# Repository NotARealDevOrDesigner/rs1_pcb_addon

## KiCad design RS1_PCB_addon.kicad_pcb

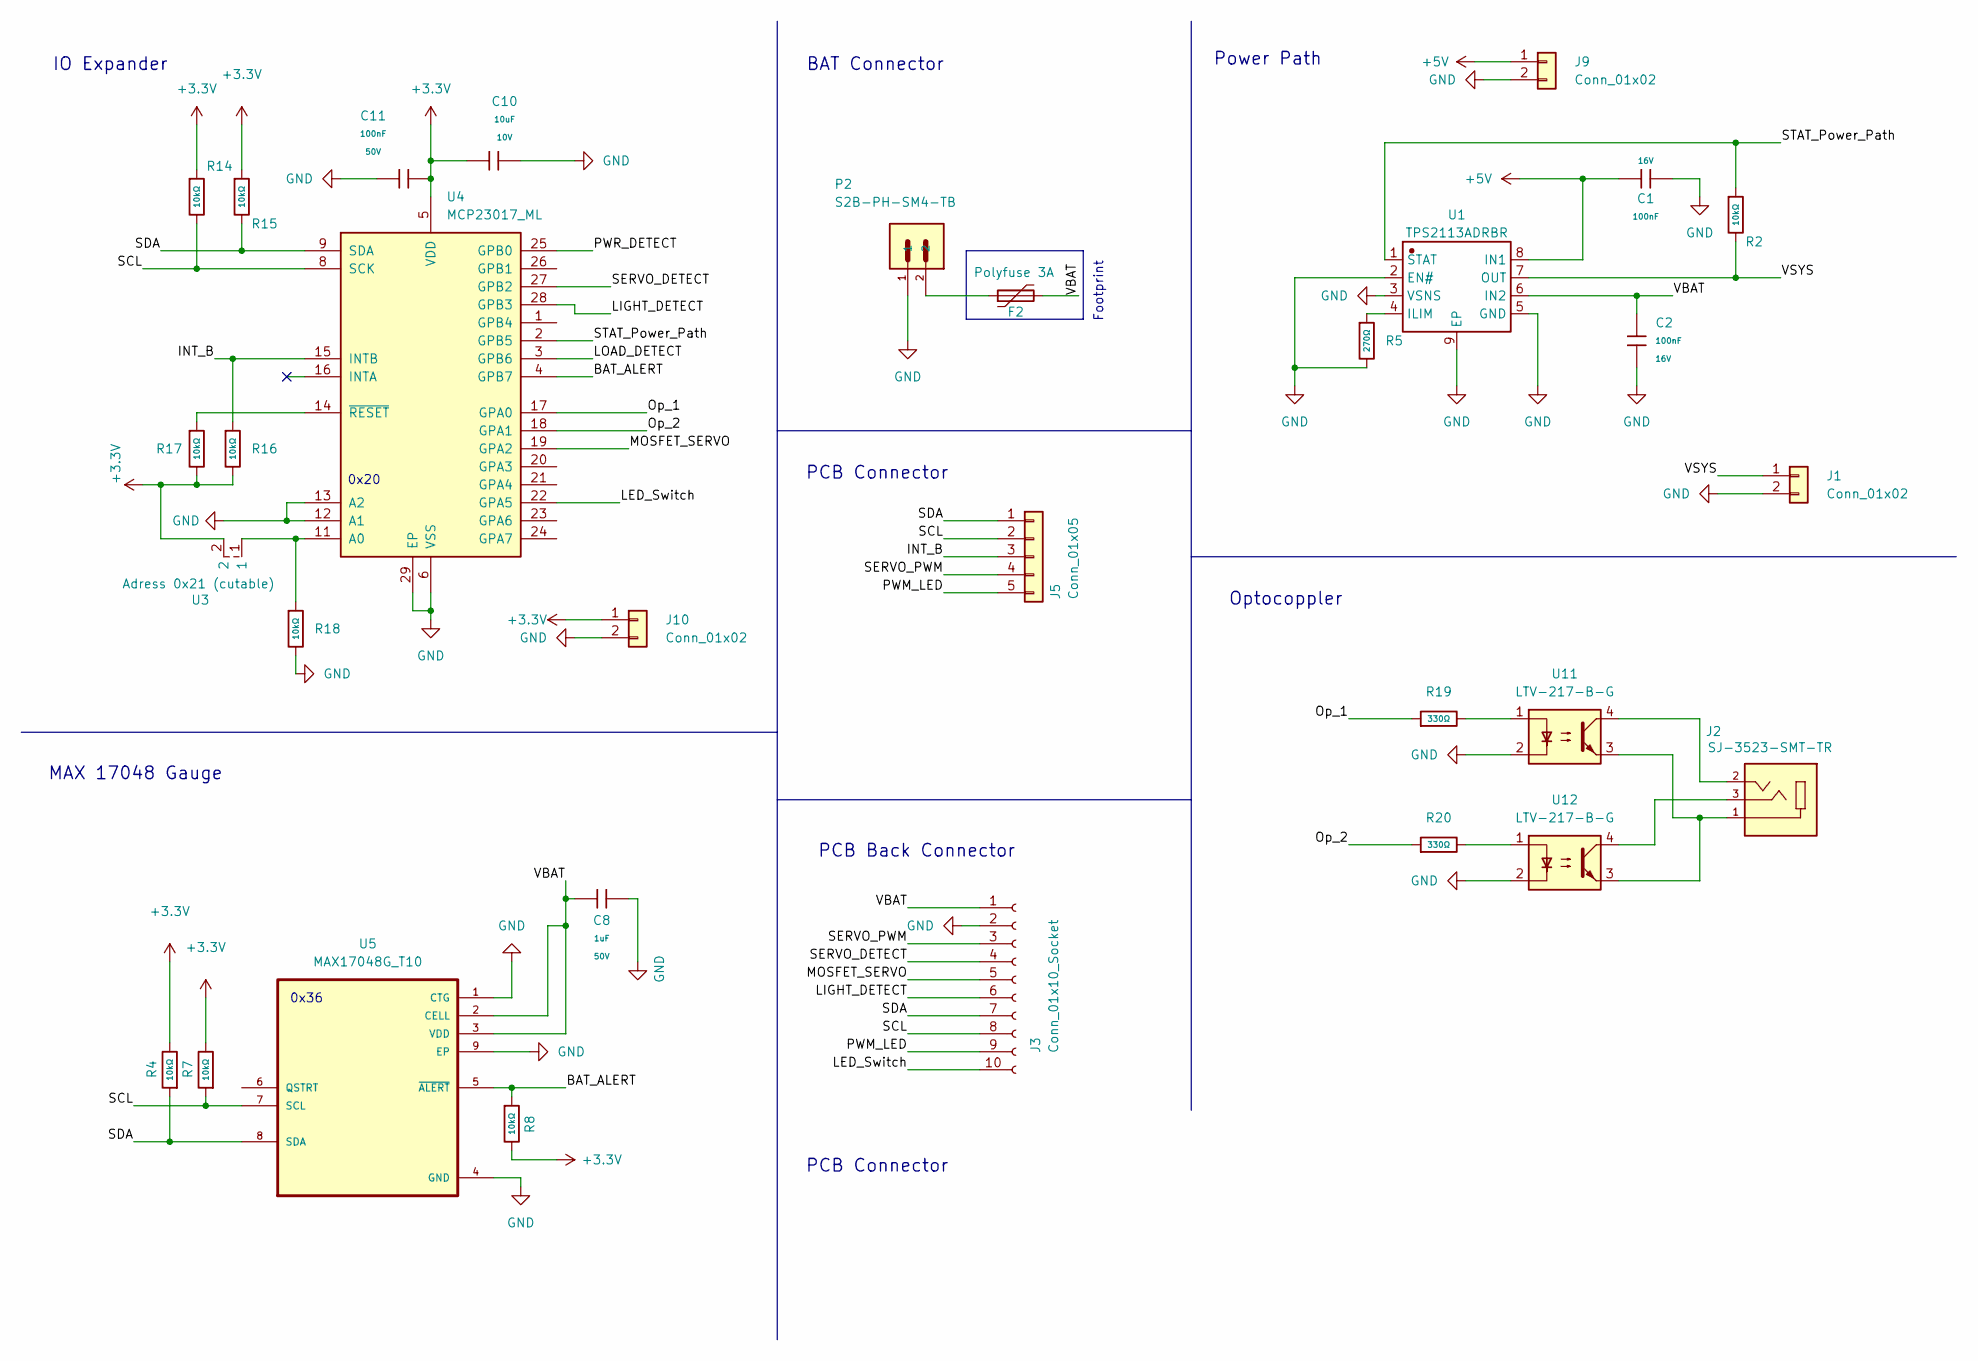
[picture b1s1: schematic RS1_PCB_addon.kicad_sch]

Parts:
C1, C2: 100nF; C_0402; Voltage Rated 16V; Tolerance ±10%; Part CL05B104KO5NNNC; LCSC C1525
C8: 1uF; C_0805; Voltage Rated 50V; Tolerance ±10%; Part CL21B105KBFNNNE; LCSC C28323
C10: 10uF; C_0603; Voltage Rated 10V; Tolerance ±10%; Part CL10A106KP8NNNC; LCSC C19702
C11: 100nF; C_0603; Voltage Rated 50V; Tolerance ±10%; Part CC0603KRX7R9BB104; LCSC C14663
F2: Polyfuse 3A; Fuse_1812_4532Metric
J1, J9, J10: Conn_01x02; PinHeader_1x02_P2.54mm_Vertical
J2: SJ-3523-SMT-TR; CUI_SJ-3523-SMT-TR
J3: Conn_01x10_Socket; PinSocket_1x10_P2.54mm_Vertical
J5: Conn_01x05; PinHeader_1x05_P2.54mm_Vertical
P2: S2B-PH-SM4-TB; JST_S2B-PH-SM4-TB
R2, R4, R7, R8, R14, R15, R16, R17, R18: 10kΩ; R_0402; Overload Voltage (Max) 50V; Tolerance ±1%; Part 0402WGF1002TCE; LCSC C25744
R5: 270Ω; R_0603; Overload Voltage (Max) 75V; Tolerance ±1%; Part 0603WAF2700T5E; LCSC C22966
R19, R20: 330Ω; R_0402; Overload Voltage (Max) 50V; Tolerance ±1%; Part 0402WGF3300TCE; LCSC C25104
U1: TPS2113ADRBR; SON-8_L3.0-W3.0-P0.65-LS3.0-BL-EP; Manufacturer Part TPS2113ADRBR
U3: Adress 0x21 (cutable); 2Pad_Cut
U4: MCP23017_ML; QFN-28-1EP_6x6mm_P0.65mm_EP4.25x4.25mm
U5: MAX17048G_T10; SON50P200X200X80-9N
U11, U12: LTV-217-B-G; SOP-4_4.4x2.6mm_P1.27mm; Part LTV-217-B-G; LCSC C115450

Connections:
+3.3V: C10.1, C11.2, J10.1, R4.2, R7.2, R8.2, R14.1, R15.1, R16.2, R17.2, U3.2, U4.5 (VDD)
+5V: C1.1, J9.1, U1.8 (IN1)
/BAT_ALERT: R8.1, U4.4 (GPB7), U5.5 (~ALERT)
/INT_B: J5.3, R16.1, U4.15 (INTB)
/LED_Switch: J3.10, U4.22 (GPA5)
/LIGHT_DETECT: J3.6, U4.28 (GPB3)
/LOAD_DETECT: U4.3 (GPB6)
/MOSFET_SERVO: J3.5, U4.19 (GPA2)
/Op_1: R19.1, U4.17 (GPA0)
/Op_2: R20.1, U4.18 (GPA1)
/PWM_LED: J3.9, J5.5
/PWR_DETECT: U4.25 (GPB0)
/SCL: J3.8, J5.2, R7.1, R14.2, U4.8 (SCK), U5.7 (SCL)
/SDA: J3.7, J5.1, R4.1, R15.2, U4.9 (SDA), U5.8 (SDA)
/SERVO_DETECT: J3.4, U4.27 (GPB2)
/SERVO_PWM: J3.3, J5.4
/STAT_Power_Path: R2.1, U1.1 (STAT), U4.2 (GPB5)
/VBAT: C2.1, C8.1, F2.2, J3.1, U1.6 (IN2), U5.2 (CELL), U5.3 (VDD)
/VSYS: J1.1, R2.2, U1.7 (OUT)
GND: C1.2, C2.2, C8.2, C10.2, C11.1, J1.2, J3.2, J9.2, J10.2, P2.1, R5.2, R18.2, U1.2 (EN#), U1.3 (VSNS), U1.5 (GND), U1.9 (EP), U4.6 (VSS), U4.12 (A1), U4.13 (A2), U4.29 (EP), U5.1 (CTG), U5.4 (GND), U5.9 (EP), U11.2, U12.2
unnamed: F2.1, P2.2
unnamed: J2.1, U11.3, U12.3
unnamed: J2.2, U11.4
unnamed: J2.3, U12.4
unnamed: R19.2, U11.1
unnamed: R20.2, U12.1
unnamed: R5.1, U1.4 (ILIM)
unnamed: R18.1, U3.1, U4.11 (A0)
unnamed: R17.1, U4.14 (~RESET)

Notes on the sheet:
PCB Back Connector
Optocoppler
BAT Connector
IO Expander
PCB Connector
0x20
Footprint
MAX 17048 Gauge
0x36
Power Path

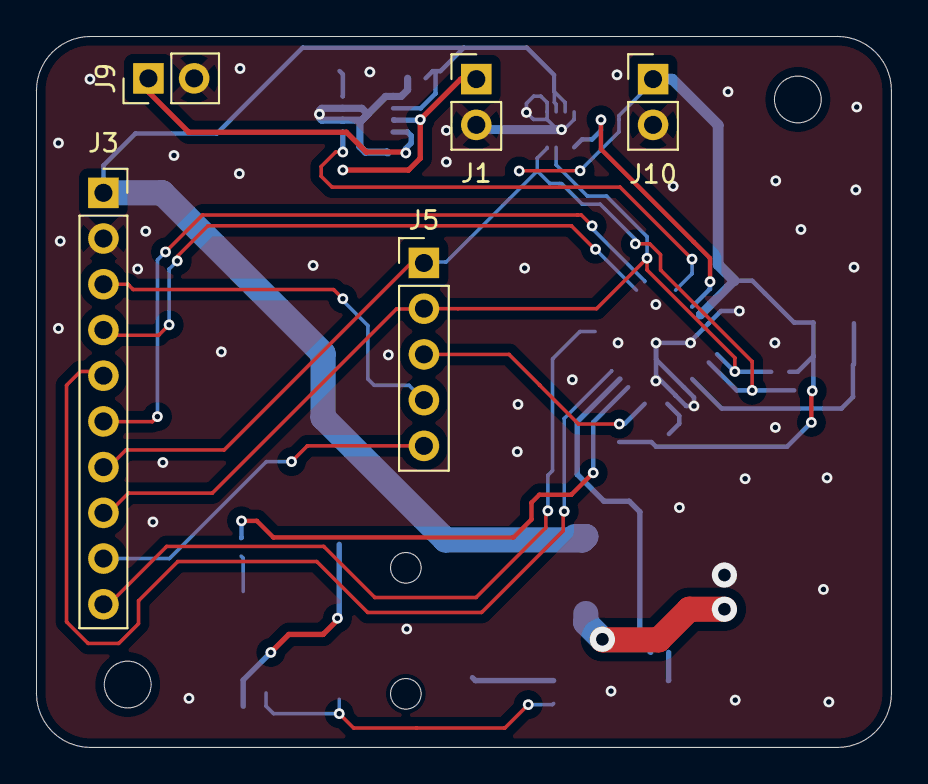
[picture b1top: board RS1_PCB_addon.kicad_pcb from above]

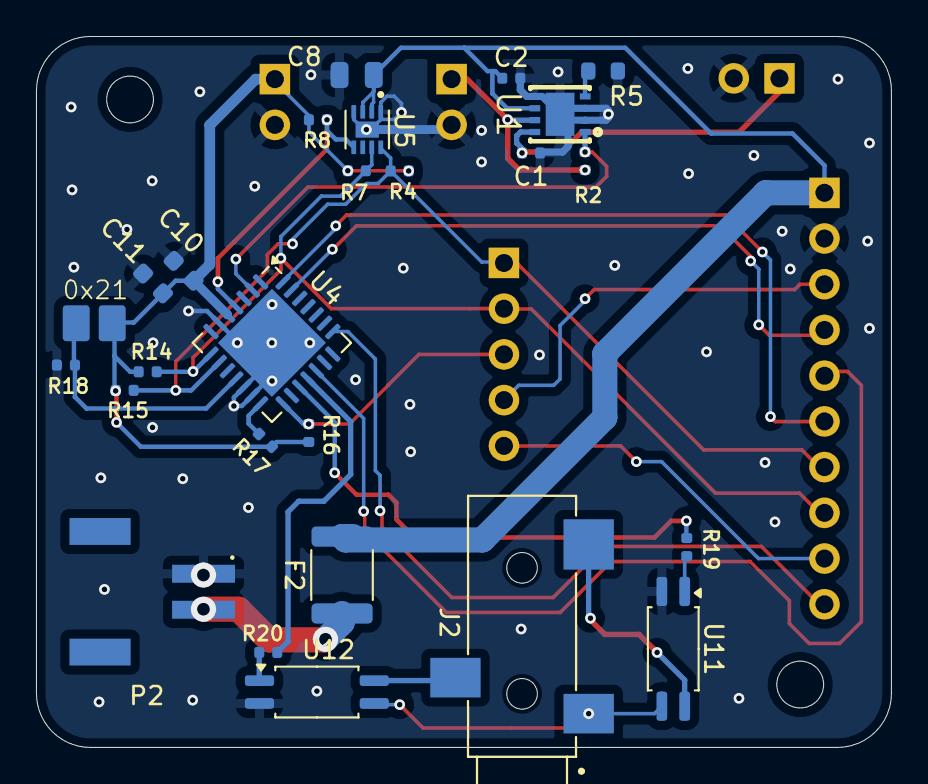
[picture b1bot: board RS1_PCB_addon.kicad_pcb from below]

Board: 2 copper layers, 47.5 x 39.5 mm, 31 parts (26 on the bottom side), 27 nets.

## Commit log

2026-01-13 init commit
2026-01-16 change edgecut
2026-01-16 change layout
2026-01-17 change pin position
2026-01-17 switch Commit
